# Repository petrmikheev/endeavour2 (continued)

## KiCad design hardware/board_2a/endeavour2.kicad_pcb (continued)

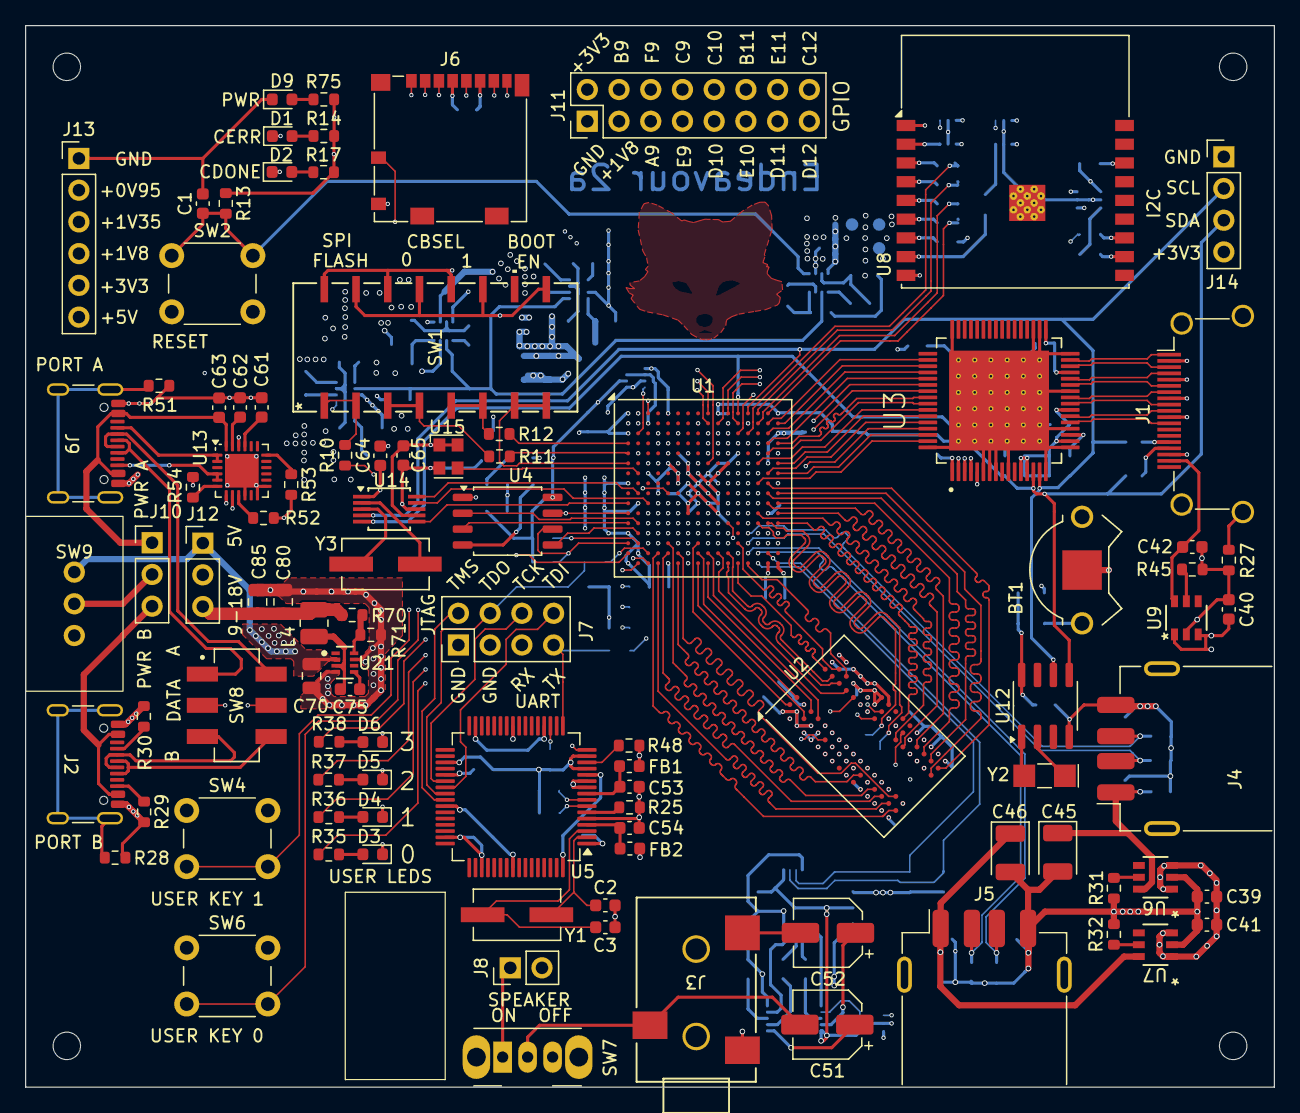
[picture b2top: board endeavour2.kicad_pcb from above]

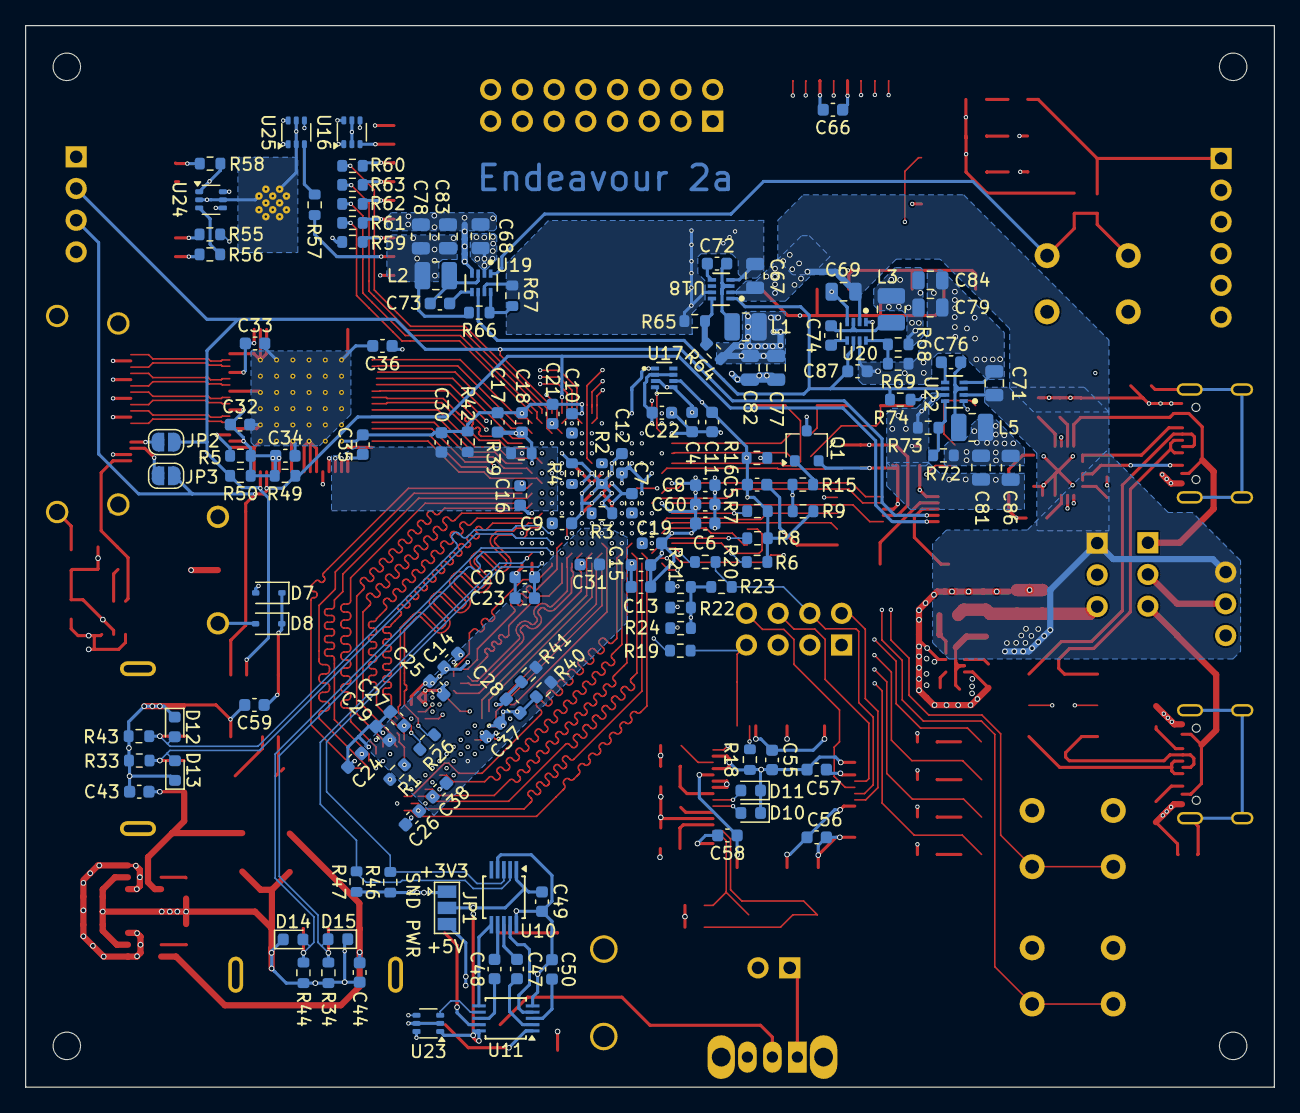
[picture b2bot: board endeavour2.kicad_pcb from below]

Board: 6 copper layers, 100.0 x 85.0 mm, 238 parts (141 on the bottom side), 257 nets.

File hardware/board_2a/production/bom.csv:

Designator,Footprint,Quantity,Value,LCSC Part #
BT1,BAT_2989,1,Battery_Cell,
"C1, C14, C17, C4, C47, C48, C49, C50, C53, C54, C61, C62, C63, C66, C87, C9",0603,16,1uF,
"C10, C13, C24, C36, C39, C40, C42",0603,7,10uF,
"C11, C23, C28, C8",0603,4,4.7uF,
"C12, C15, C18, C27, C32, C33, C34, C35, C37, C38, C7",0603,11,0.01uF,
"C16, C6",0603,2,47uF,
"C19, C20, C21, C22, C25, C26, C29, C30, C31, C41, C43, C44, C5, C55, C56, C57, C58, C59, C60, C64, C65, C72, C73, C74, C75, C76",0603,26,0.1uF,
"C2, C3",0603,2,27pF,
"C45, C46",CP_EIA-3528-12_Kemet-T,2,100uF,
"C51, C52",CP_Elec_5x5.3,2,100uF,
"C67, C68, C69, C70, C71, C77, C78, C79, C80, C81, C82, C83, C84, C85, C86",0805,15,22uF,
"D1, D2, D3, D4, D5, D6, D9",0603,7,LED,
"D10, D11, D12, D13, D14, D15",0603,6,D_TVS,
"D7, D8",D_SOD-323,2,D,
"FB1, FB2",0603,2,~,
J1,HDMI_A_Amphenol_10029449-x01xLF_Horizontal,1,HDMI_A,
J10,PinHeader_1x03_P2.54mm_Vertical,1,jumper_power_source,
J11,PinHeader_2x08_P2.54mm_Vertical,1,Conn_GPIO,
J12,PinHeader_1x03_P2.54mm_Vertical,1,jumper_5v,
J13,PinHeader_1x06_P2.54mm_Vertical,1,Conn_power,
J14,PinHeader_1x04_P2.54mm_Vertical,1,Conn_01x04_Pin,
"J2, J9",USB_C_Receptacle_GCT_USB4105-xx-A_16P_TopMnt_Horizontal,2,USB_C_Receptacle_USB2.0,
J3,SJ-3523-SMT_CUD,1,SJ-3523-SMT,
"J4, J5",USB_A_Receptacle_GCT_USB1046,2,USB_A,
J6,microSD_HC_Molex_104031-0811,1,Micro_SD_Card_Det2,
J7,PinHeader_2x04_P2.54mm_Vertical,1,Conn_02x04_Odd_Even,
J8,PinHeader_1x02_P2.54mm_Vertical,1,Conn_01x02,
JP1,SolderJumper-3_P1.3mm_Open_Pad1.0x1.5mm,1,snd_power,
"JP2, JP3",SolderJumper-2_P1.3mm_Open_RoundedPad1.0x1.5mm,2,Jumper_2_Bridged,
"L1, L2, L3",1008,3,2.2uH,
"L4, L5",1008,2,4.7uH,
Q1,SC-59,1,Q_NPN_BEC,
R1,0603,1,240,
"R10, R11, R12, R13, R16, R18, R2, R21, R22, R23, R24, R3, R4, R54, R58, R59, R6, R7, R71, R73, R74, R8, R9",0603,23,10K,
"R14, R17, R35, R36, R37, R38, R75",0603,7,25,
R15,0603,1,100K,
"R19, R20, R55, R56, R57, R60, R61, R62, R63",0603,9,75,
R25,0603,1,12K,
R26,0603,1,100,
"R27, R28, R51",0603,3,1M,
"R29, R30, R49, R50",0603,4,5.1K,
"R31, R32",0603,2,60K,
"R33, R34, R43, R44",0603,4,15K,
"R39, R40, R41, R42, R48, R52, R53",0603,7,1K,
R45,0603,1,200K,
"R46, R47",0603,2,1.5K,
R5,0603,1,510,
R64,0603,1,23.2K,
"R65, R68",0603,2,40.2K,
R66,0603,1,24.9K,
"R67, R69",0603,2,20K,
R70,0603,1,73.2K,
R72,0603,1,45.3K,
SW1,SPDT_204-124_CTS,1,204-124ST,
"SW2, SW4, SW6",SW_PUSH_6mm,3,SW_Push,
SW7,SW_Slide_SPDT_Angled_CK_OS102011MA1Q,1,SW_SPDT,
SW8,SW_JS202011SCQN,1,~,
SW9,mss3111,1,SW_SPDT,
U1,BGA-256_14.0x14.0mm_Layout16x16_P0.8mm_Ball0.45mm_Pad0.32mm_NSMD,1,Ti60F256,
U10,MSOP-10_3x3mm_P0.5mm,1,MCP4728,
U11,TSSOP-10_3x3mm_P0.5mm,1,LM4811,
U12,SOIC-8_3.9x4.9mm_P1.27mm,1,PCF85063AT/AY,
U13,QFN-24-1EP_4x4mm_P0.5mm_EP2.7x2.7mm,1,STUSB4500QTR,
U14,MSOP-10_3x3mm_P0.5mm,1,Si5351A-B-GT,
U15,Oscillator_SMD_Kyocera_KC2520Z-4Pin_2.5x2.0mm,1,MC2520Z 25MHz,
"U16, U23, U24, U25",SOT-363_SC-70-6,4,SN74LVC1T45DCK,
U17,SOTFL50P160X60-8N,1,TPS2116DRLR,
"U18, U19, U20, U21, U22",DRL0008A-MFG,5,TPS562211DRLR,
U2,BGA-96_9.0x13.5mm_Layout2x3x16_P0.8mm,1,IM8G16D3FFBG,
U3,IC_TFP410PAP,1,TFP410PAP,
U4,SOIC-8_5.23x5.23mm_P1.27mm,1,W25Q128JWS,
U5,LQFP-64_10x10mm_P0.5mm,1,FT2232HL,
"U6, U7, U9",SOT26_DIO,3,AP22653W6-7,
U8,ESP32-C3-WROOM-02,1,ESP32-C3-WROOM-02-N4,
Y1,XTAL_ECS-120-20-3X-TR,1,12MHz,
Y2,Crystal_SMD_MicroCrystal_CC7V-T1A-2Pin_3.2x1.5mm_HandSoldering,1,Crystal,
Y3,XTAL_ECS-120-20-3X-TR,1,25MHz,

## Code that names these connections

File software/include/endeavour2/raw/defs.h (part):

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#define GPIO_KEY2             (1<<6)
#define GPIO(x)               (1<<((x)+7))  // x in range 1-13
#define GPIO_ESP32_HS         (1<<22)
#define GPIO_ESP32_EN         (1<<23)
#define GPIO_ESP32_SPI_BOOT   (1<<24)
#define GPIO_ESP32_DR         (1<<27)
#define GPIO_SPI_FLASH_EN     (1<<28)
#define GPIO_BOOT_EN          (1<<29)
#define GPIO_CBSEL0           (1<<30)
#define GPIO_CBSEL1           (1<<31)

// BOARD_CPU_FEATURES flags
#define CPU_FEATURES_ZBA        1  // Address calculation extension.
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
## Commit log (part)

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2025-02-15 Add VexiiRiscv submodule
2025-02-15 Add initial version of hardware/board_2a
2025-02-16 PCB update
2025-02-16 Update hardware/board_2a
2025-05-04 Initial SoC implementation
2025-05-04 Production files in ../hardware/board_2a
2025-05-04 Fix bug in ddr3_adapter
2025-05-04 Reduce RAM frequency from 400 MHz to 333 MHz to avoid memory errors; improve memtest
2025-05-04 sdcard & usb
2025-05-04 minor bugfix
2025-05-04 Add gen_hex.py
2025-05-04 Multicore support
2025-05-04 Add audio controller; add frequency counters; update ddr3_adapter according to on-device debugging results
2025-05-04 DDR frontend for sdcard; now SDR104 is supported; sdcard read benchmark shows 58 MB/s (limited by APB3 interface)
2025-05-04 Autoboot option in bios
2025-05-04 Load BIOS image from SPI flash on boot.
2025-05-04 Make ddr tac shift configurable
2025-05-04 sdwrite test
2025-05-04 Fix bug in bios/ams.S - variables which are used in bios.h must have fixed address
2025-05-04 linux drivers; textwm2
2025-05-04 Refactoring and new ROM implementation
2025-05-04 Update textwm
2025-05-04 Set DDR3 controller timings preset from 800D to 800E
2025-05-04 Disable withRvZb in "full" core
2025-05-04 Add video controller
2025-05-04 Update VexiiRiscv
2025-05-04 Started bios implementation by copying code from endeavour1
2025-05-04 Fixed sdcard read/write functions (controller returns big endian instead of little endian); added EXT2 support, loading BMP wallpaper; added support of 4-color characters.
2025-05-04 Update software/bios, add benchmarks
2025-05-04 Add FPU and FPU benchmarks
2025-05-04 Remove kicad_prl from repo
2025-05-04 Add usb keyboard support; increase sdcard controller clk from 100mhz to 200mhz
2025-05-04 update software/bios; add console.c and improve memtest
2025-05-04 Change extension order in ISA string
2025-05-04 Decouple sdcard clk and ram clk; disable SRD104 mode - for unknown reason write doesn't work on some sdcards.
2025-05-04 Fix bug in ddr3 adapter
2025-05-04 linux bootloader; maybe fixed a bug with incorrect reported cpu frequency
2025-05-04 add some buildroot-related configs and scripts
2025-05-04 Expose cbsel, boot_en, spi_en to software; don't instantiate video controller if ramSize < 8MB
2025-05-04 Reduce reset duration in simulation
2025-05-04 Update textwm; show logo on ^[?314e
2025-05-04 rtl: add I2C controller, connect ESP32 UART; bios: add "date" command
2025-05-04 Fix bug in video controller - first text line was loaded from RAM only partially
2025-05-10 Add readme
2025-05-13 Add RTC driver
2025-05-21 Add GPLv3 license
2025-06-04 Support debugging via openocd
2025-06-04 Add audio driver
2025-06-11 Framebuffer driver
2025-06-13 Xorg support
2025-06-13 Add more pictures to README
2025-06-16 Properly delegate exceptions to supervisor; linux kernel can emulate misaligned access
2025-06-17 Remove debug message in display driver
2025-06-17 Add new picture to readme
2025-12-26 Minor change in textwm startup script
2025-12-26 A few utils for experimenting with onboard ESP32 module
2025-12-26 Case for endeavour2a board; Freecad model for 3d printing
2025-12-30 Start /usr/bin/login instead of just sh in S10textwm. /usr/bin/login in particular unblocks SIGINT (which is masked in init process and its children by default), so ctrl+c can be used in shells.
2026-01-23 Update xorg.cong (now xrandr works)
2026-01-23 Change textwm2 input mapping for backspace: \b -> \x7f
2026-01-23 Add hardware/board_2b
2026-01-23 Add spi controller with fifo; connect esp32
2026-01-23 Rename hardware/extension -> ext_2a_to_2b
2026-01-23 Update linux drivers
2026-01-23 Fix in textwm2: don't rely that /dev/input/event0 is a keyboard
2026-01-28 Add DMA controller; update VexiiRiscv; CPU frequency decreased 220 MHz -> 200 MHz
2026-02-05 Update hardware/board_2b
2026-02-05 Add more `fence` in software/bios
2026-02-06 Set allowed dma buffer range from [128, 8192] to [0, 8192-128]
2026-02-07 gpio controller ; spi controller for e2417 display ; bugfixes
2026-02-08 Increase cpu freq 200 -> 207 MHz and ram freq 333 -> 400 MHz ; merge clk_sdctrl into clk_cpu
2026-02-08 Check DTB crc32 when boot linux via UART
2026-02-11 Optimize usage of Ti60 memory cells; add a.param=2 in DmaController and VideoController
2026-02-21 Add rtl/endeavour2b; fix bug in gpio controller
2026-02-25 Fix bug in videcontroller - wrong pixel on right side of the screen in resolution 800x600
2026-02-25 Fix gpio pin numbers in defs.h
2026-02-25 Add custom instruction MIXRGB
2026-02-25 Add DMA bindings to display driver
2026-02-25 Add low level audio interface /dev/audio. Similar to /dev/dsp. Non-standard, but has very low overhead.
2026-02-25 Add DMA interrupt in DTS
2026-02-25 Change audio controller to use 16-bit signed values (with 4 less significant bits ignored) instead of 12-bit unsigned values.
2026-02-26 Add MIXRGB instruction to DMA controller
2026-02-26 Remove deprecated gpio driver; comment some debug output in uart driver.
2026-03-01 Workaround for a bug in Efinity; fixed another bug in DmaController; Disabled custom instruction MIXRGB because DMA_MIXRGB can be used instead.
2026-03-02 Add instructions DMA_LOADMAP, DMA_MAP1R2, DMA_MAP1R4
2026-03-03 Minor change in textwm2 - use ctrl+tab to hide text layer
2026-03-04 Add X11 fbdev driver which uses endeavour DMA to move windows
2026-03-04 Update placement seed in endeavour2a. Reportex max cpu freq is 207.297 MHz.
2026-03-04 Comment some debug output in display driver
2026-03-04 Remove hardware/ext_2a_to_2b (it was for testing, not needed anymore)
2026-03-04 Update placement seed in endeavour2b
2026-03-09 Update BIOS. Add EDID parsing, battery status, E-Ink display support.
2026-03-13 Update board_2b case 3d model
2026-03-13 Update fifo_spi driver; comment debug prints in uart driver
2026-03-13 Some test code in software/raw_examples
2026-03-13 Add patch for esp-hosted-ng kernel module. Update kernel and buildroot configs. Now ESP32 works as WiFi adapter in endeavour2.
2026-03-13 Add patch for quake2sdl
2026-03-13 More reliable PLL initialization
2026-03-23 Add a link to blog.mikhe.ch
